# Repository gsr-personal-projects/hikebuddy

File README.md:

# hikebuddy
An ESP32 based hike/bike computer with weather monitoring, GPS tracking and BLE sensor support (and a general purpose development board)

This project has moved to its own home at https://github.com/hikebuddy32.

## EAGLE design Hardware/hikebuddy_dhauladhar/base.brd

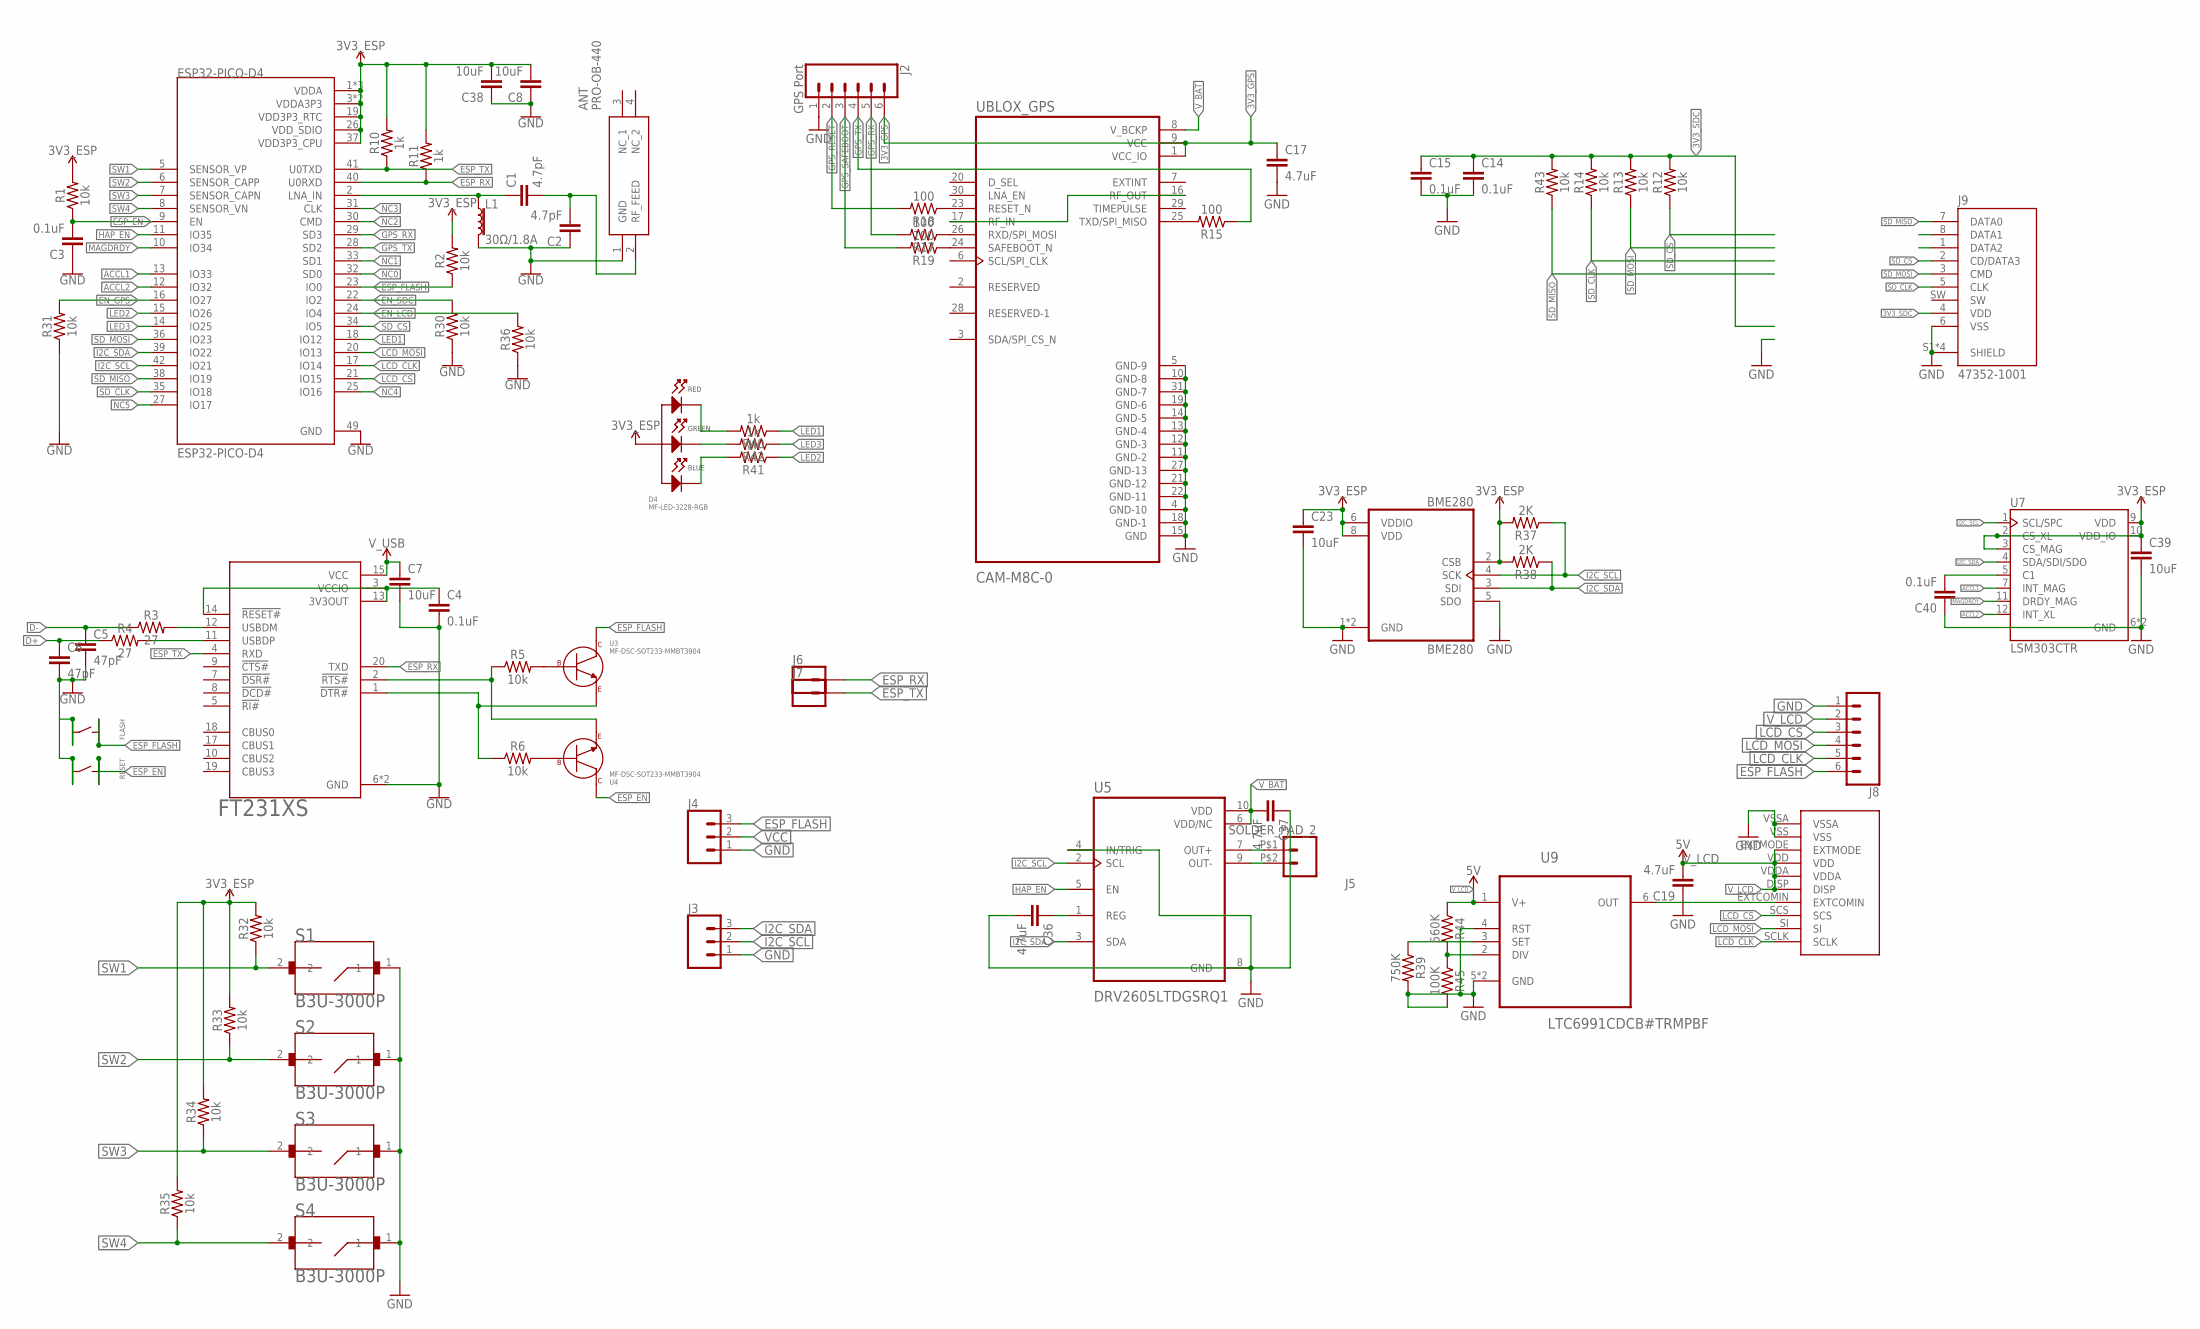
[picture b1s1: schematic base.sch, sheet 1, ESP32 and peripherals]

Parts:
ANT: PRO-OB-440; PRO-OB-440_1
BME280: BME280; PSON65P250X250X100-8N
C1, C2: 4.7pF; C0603
C3, C4, C14, C15, C40: 0.1uF; C0603
C5, C6: 47pF; C0603
C7, C8, C23, C38, C39: 10uF; C0603
C17, C19, C36, C37: 4.7uF; C0603
D4: MF-LED-3228-RGB; PLCC4
ESP32-PICO-D4: ESP32-PICO-D4; PQFN50P700X700X104-49N
FLASH: MF-SW-TACT-4.2MM; TACT4.2MM
FT231: FT231XS; TSSOP20
J2: GPS Port; 1X06_LOCK
J3, J4: CONN_03LOCK; 1X03_LOCK
J5: SOLDER_PAD_2
J6, J7: CONN_01; 1X01
J8: CONN_06LOCK; 1X06_LOCK
J9: 47352-1001; MOLEX_47352-1001
L1: 30Ω/1.8A; L0603; MPN 744761016C
R1, R2, R5, R6, R12, R13, R14, R30, R31, R32, R33, R34, R35, R36, R43: 10k; R0603
R3, R4: 27; R0603
R10, R11, R40, R41, R42: 1k; R0603
R15, R17, R18, R19: 100; R0603
R37, R38: 2K; R0603
R39: 750K; R0603
R44: 560K; R0603
R45: 100K; R0603
RESET: MF-SW-TACT-4.2MM; TACT4.2MM
S1, S2, S3, S4: B3U-3000P; SW_B3U-3000P
U3, U4: MF-DSC-SOT233-MMBT3904; SOT-23-3
U5: DRV2605LTDGSRQ1; SOP50P490X110-10N
U7: LSM303CTR; LGA-12
U9: LTC6991CDCB#TRMPBF; DFN
U$5: 51441-1093; FH12-10S-0.5SH; MPN 51441-1093
UBLOX_GPS: CAM-M8C-0; LCC100P960X1400X210-31N

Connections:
3V3_GPS: C17.1, J2.6, UBLOX_GPS.1 (VCC_IO), UBLOX_GPS.9 (VCC); also elsewhere on the board
3V3_SDC: C14.1, C15.1, J9.4 (VDD), R12.2, R13.2, R14.2, R43.2; also elsewhere on the board
ACCL1: ESP32-PICO-D4.13 (IO33), U7.7 (INT_MAG)
ACCL2: ESP32-PICO-D4.12 (IO32), U7.12 (INT_XL)
D+: C6.1, R4.1; also elsewhere on the board
D-: C5.1, R3.1; also elsewhere on the board
EN_GPS: ESP32-PICO-D4.16 (IO27), R31.2; also elsewhere on the board
EN_LCD: ESP32-PICO-D4.24 (IO4), R36.2; also elsewhere on the board
EN_SDC: ESP32-PICO-D4.22 (IO2), R30.2; also elsewhere on the board
ESP_EN: C3.2, ESP32-PICO-D4.9 (EN), R1.1, RESET.P$1, RESET.P$2, U4.P$3 (COLLECTOR)
ESP_FLASH: ESP32-PICO-D4.23 (IO0), FLASH.P$1, FLASH.P$2, J4.3, J8.6, R2.1, U3.P$3 (COLLECTOR)
ESP_RX: ESP32-PICO-D4.40 (U0RXD), FT231.20 (TXD), J6.1, R11.1
ESP_TX: ESP32-PICO-D4.41 (U0TXD), FT231.4 (RXD), J7.1, R10.1
GND: ANT.1 (GND), BME280.1 (GND), BME280.5 (SDO), BME280.7 (GND), C2.1, C3.1, C4.2, C5.2, C6.2, C7.2, C8.1, C14.2, C15.2, C17.2, C19.1, C23.2, C36.2, C37.1, C38.1, C39.2, C40.1, ESP32-PICO-D4.49 (GND), FLASH.P$3, FLASH.P$4, FT231.6 (GND), FT231.16 (GND), J2.1, J3.1, J4.1, J8.1, J9.6 (VSS), J9.S1 (SHIELD), J9.S2 (SHIELD), J9.S3 (SHIELD), J9.S4 (SHIELD), L1.2, R30.1, R31.1, R36.1, R39.2, R45.2, RESET.P$3, RESET.P$4, S1.1, S2.1, S3.1, S4.1, U5.4 (IN/TRIG), U5.8 (GND), U7.6 (GND), U7.8 (GND), U9.4 (RST), U9.5 (GND), U9.7 (GND), U$5.VSS, U$5.VSSA, UBLOX_GPS.4 (GND-10), UBLOX_GPS.5 (GND-9), UBLOX_GPS.10 (GND-8), UBLOX_GPS.11 (GND-2), UBLOX_GPS.12 (GND-3), UBLOX_GPS.13 (GND-4), UBLOX_GPS.14 (GND-5), UBLOX_GPS.15 (GND), UBLOX_GPS.18 (GND-1), UBLOX_GPS.19 (GND-6), UBLOX_GPS.21 (GND-12), UBLOX_GPS.22 (GND-11), UBLOX_GPS.27 (GND-13), UBLOX_GPS.31 (GND-7); also elsewhere on the board
GPS_RESET: J2.2, R18.2
GPS_RX: ESP32-PICO-D4.29 (SD3), J2.5, R17.2
GPS_SAFEBOOT: J2.3, R19.2
GPS_TX: ESP32-PICO-D4.28 (SD2), J2.4, R15.1
HAP_EN: ESP32-PICO-D4.11 (IO35), U5.5 (EN)
I2C_SCL: BME280.4 (SCK), ESP32-PICO-D4.42 (IO21), J3.2, R37.1, U5.2 (SCL), U7.1 (SCL/SPC); also elsewhere on the board
I2C_SDA: BME280.3 (SDI), ESP32-PICO-D4.39 (IO22), J3.3, R38.1, U5.3 (SDA), U7.4 (SDA/SDI/SDO); also elsewhere on the board
LCD_CLK: ESP32-PICO-D4.17 (IO14), J8.5, U$5.SCLK
LCD_CS: ESP32-PICO-D4.21 (IO15), J8.3, U$5.SCS
LCD_MOSI: ESP32-PICO-D4.20 (IO13), J8.4, U$5.SI
LED1: ESP32-PICO-D4.18 (IO12), R40.1
LED2: ESP32-PICO-D4.15 (IO26), R41.1
LED3: ESP32-PICO-D4.14 (IO25), R42.1
MAGDRDY: ESP32-PICO-D4.10 (IO34), U7.11 (DRDY_MAG)
unnamed: C1.1, ESP32-PICO-D4.2 (LNA_IN), L1.1
unnamed: ANT.2 (RF_FEED), C1.2, C2.2
unnamed: R5.2, U3.P$1 (BASE)
unnamed: R6.2, U4.P$1 (BASE)
unnamed: C4.1, FT231.3 (VCCIO), FT231.13 (3V3OUT), FT231.14 (!RESET#)
unnamed: FT231.12 (USBDM), R3.2
unnamed: FT231.11 (USBDP), R4.2
unnamed: FT231.2 (!RTS#), R5.1, U4.P$2 (EMITTER)
unnamed: FT231.1 (!DTR#), R6.1, U3.P$2 (EMITTER)
unnamed: C40.2, U7.5 (C1)
unnamed: D4.P$2 (CATHODE_RED), R40.2
unnamed: R15.2, UBLOX_GPS.25 (TXD/SPI_MISO)
unnamed: R17.1, UBLOX_GPS.26 (RXD/SPI_MOSI)
unnamed: D4.P$3 (CATHODE_GREEN), R42.2
unnamed: D4.P$4 (CATHODE_BLUE), R41.2
unnamed: UBLOX_GPS.16 (RF_OUT), UBLOX_GPS.17 (RF_IN)
unnamed: U9.6 (OUT), U$5.EXTCOMIN
unnamed: R18.1, UBLOX_GPS.23 (RESET_N)
unnamed: R19.1, UBLOX_GPS.24 (SAFEBOOT_N)
unnamed: R39.1, U9.3 (SET)
unnamed: C36.1, U5.1 (REG)
unnamed: R44.2, R45.1, U9.2 (DIV)
unnamed: J5.P$2 (2), U5.9 (OUT-)
unnamed: J5.P$1 (1), U5.7 (OUT+)
NC0: ESP32-PICO-D4.32 (SD0)
NC1: ESP32-PICO-D4.33 (SD1)
NC2: ESP32-PICO-D4.30 (CMD)
NC3: ESP32-PICO-D4.31 (CLK)
NC4: ESP32-PICO-D4.25 (IO16)
NC5: ESP32-PICO-D4.27 (IO17)
SD_CLK: ESP32-PICO-D4.35 (IO18), J9.5 (CLK), R14.1
SD_CS: ESP32-PICO-D4.34 (IO5), J9.2 (CD/DATA3), R12.1
SD_MISO: ESP32-PICO-D4.38 (IO19), J9.7 (DATA0), R43.1
SD_MOSI: ESP32-PICO-D4.36 (IO23), J9.3 (CMD), R13.1
SW1: ESP32-PICO-D4.5 (SENSOR_VP), R32.1, S1.2
SW2: ESP32-PICO-D4.6 (SENSOR_CAPP), R33.1, S2.2
SW3: ESP32-PICO-D4.7 (SENSOR_CAPN), R34.1, S3.2
SW4: ESP32-PICO-D4.8 (SENSOR_VN), R35.1, S4.2
VCC: BME280.2 (CSB), BME280.6 (VDDIO), BME280.8 (VDD), C8.2, C23.1, C38.2, C39.1, D4.P$1 (ANODE), ESP32-PICO-D4.1 (VDDA), ESP32-PICO-D4.3 (VDDA3P3), ESP32-PICO-D4.4 (VDDA3P3), ESP32-PICO-D4.19 (VDD3P3_RTC), ESP32-PICO-D4.26 (VDD_SDIO), ESP32-PICO-D4.37 (VDD3P3_CPU), ESP32-PICO-D4.43 (VDDA), ESP32-PICO-D4.46 (VDDA), J4.2, R1.2, R2.2, R10.2, R11.2, R32.2, R33.2, R34.2, R35.2, R37.2, R38.2, U7.2 (CS_XL), U7.3 (CS_MAG), U7.9 (VDD), U7.10 (VDD_IO); also elsewhere on the board
V_BAT: C37.2, U5.6 (VDD/NC), U5.10 (VDD), UBLOX_GPS.8 (V_BCKP); also elsewhere on the board
V_LCD: C19.2, J8.2, R44.1, U9.1 (V+), U$5.DISP, U$5.EXTMODE, U$5.VDD, U$5.VDDA; also elsewhere on the board
V_USB: C7.1, FT231.15 (VCC); also elsewhere on the board

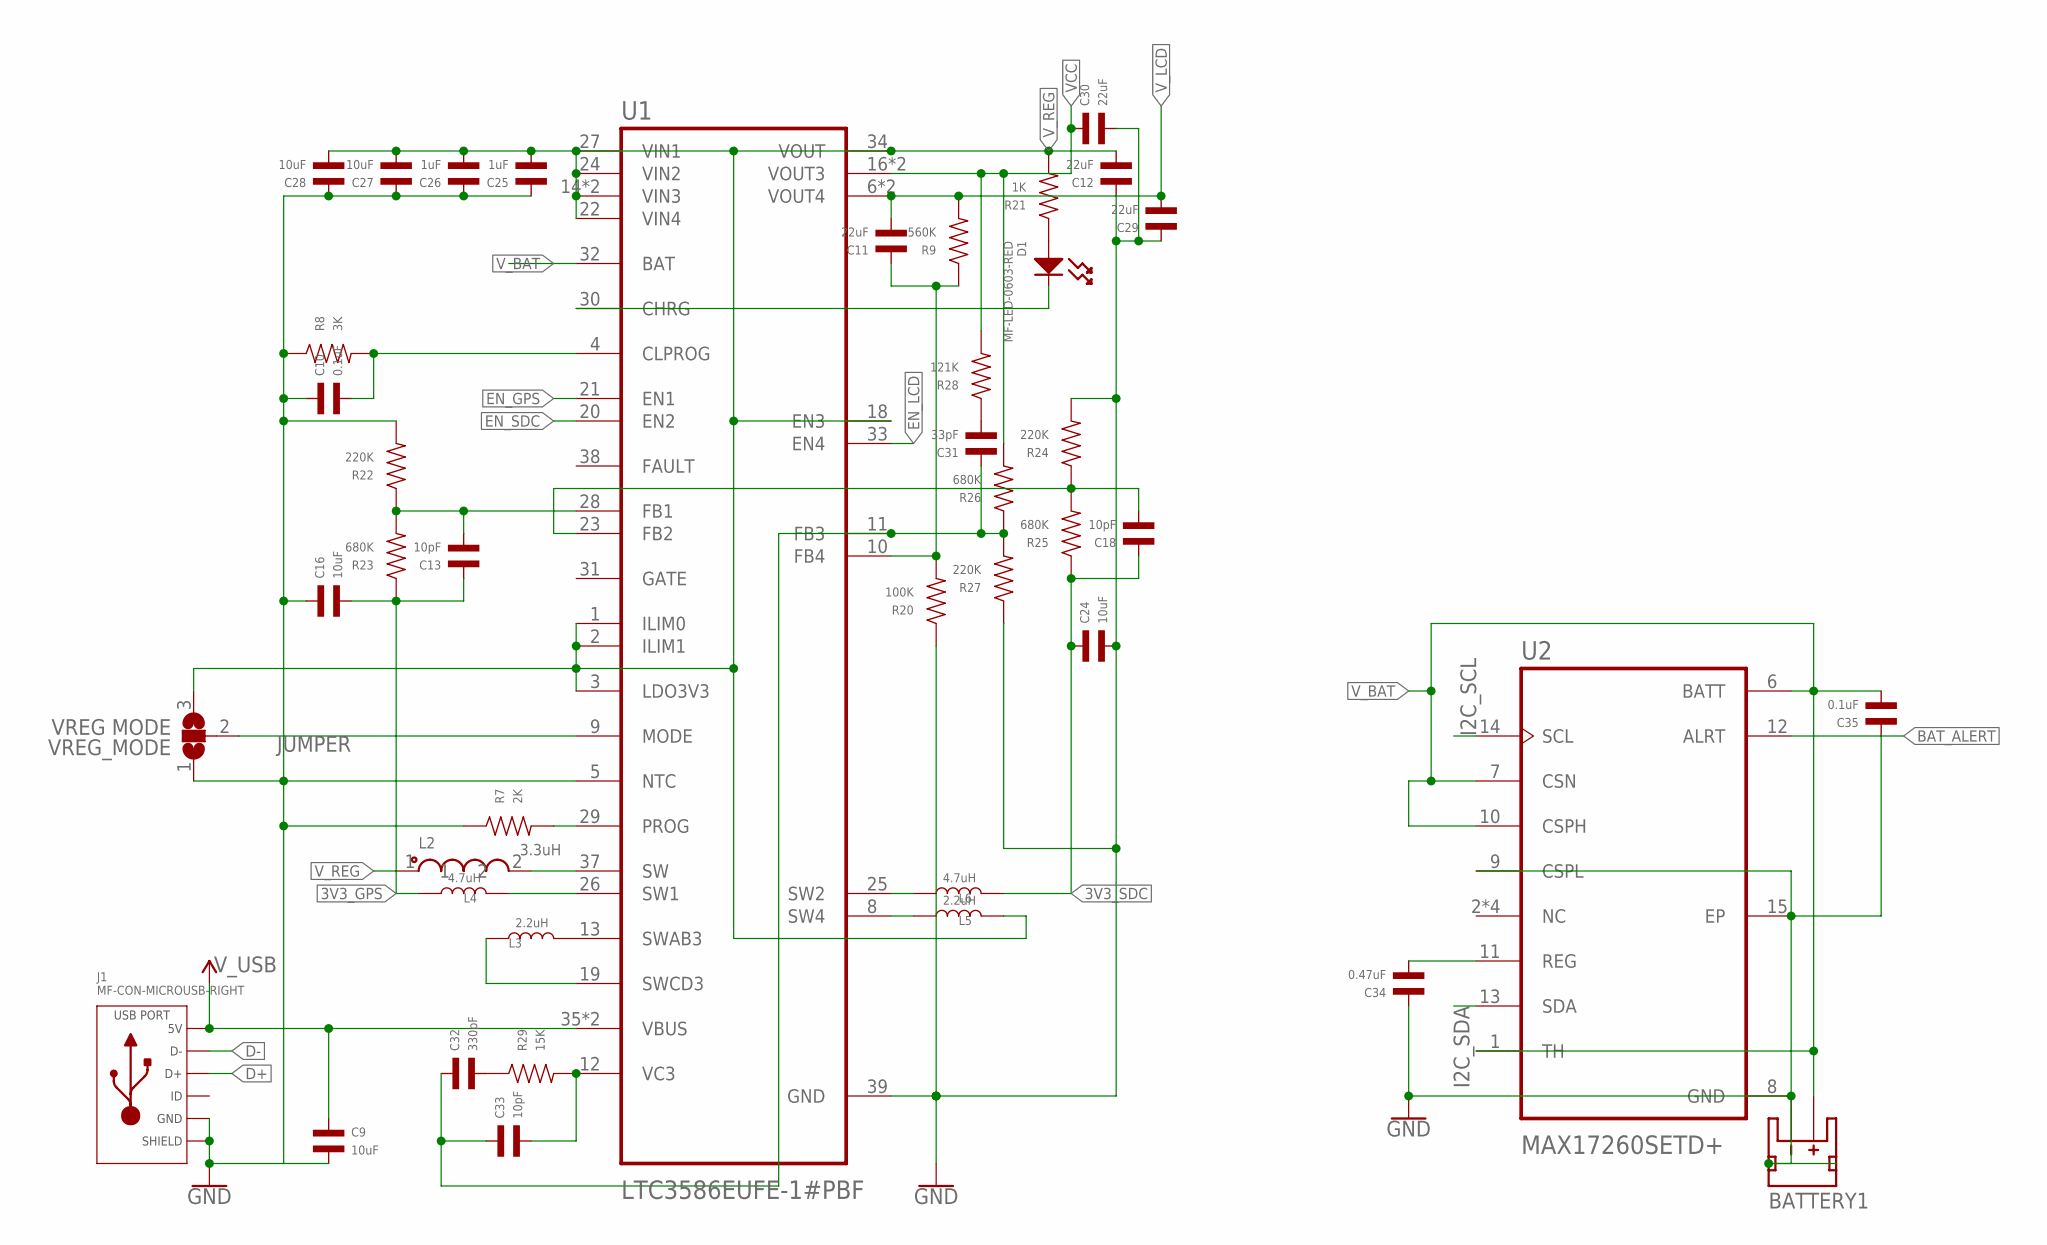
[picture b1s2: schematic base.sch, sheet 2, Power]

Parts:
BATTERY1: JST_2MM_MALE; JST-2-SMD
C9: 10uF; C1206
C10, C35: 0.1uF; C0603
C11, C12, C29, C30: 22uF; C0603
C13, C18, C33: 10pF; C0603
C16, C24, C27, C28: 10uF; C0603
C25, C26: 1uF; C0603
C31: 33pF; C0603
C32: 330pF; C0603
C34: 0.47uF; C0603
D1: MF-LED-0603-RED; LED0603
J1: MF-CON-MICROUSB-RIGHT; MICROUSB-RIGHT
L2: 3.3uH; INDP_LPS4018-472MRB; MPN LPS4018-472MRB
L3, L5: 2.2uH; L1210; MPN L1210R2R2MDWIT
L4, L6: 4.7uH; L1210; MPN L1210R4R7MDWIT
R7: 2K; R0603
R8: 3K; R0603
R9: 560K; R0603
R20: 100K; R0603
R21: 1K; R0603
R22, R24, R27: 220K; R0603
R23, R25, R26: 680K; R0603
R28: 121K; R0603
R29: 15K; R0603
U1: LTC3586EUFE-1#PBF; QFN40P600X400X80-39N
U2: MAX17260SETD+; SON40P300X300X80-15N
VREG_MODE: VREG MODE; SJ_2

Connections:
3V3_GPS: C13.P$1, C16.P$2, L4.P$1, R23.P$1; also elsewhere on the board
3V3_SDC: C18.P$1, C24.P$1, L6.P$2, R25.P$1; also elsewhere on the board
BAT_ALERT: U2.12 (ALRT)
D+: J1.3 (D+); also elsewhere on the board
D-: J1.2 (D-); also elsewhere on the board
EN_GPS: U1.21 (EN1); also elsewhere on the board
EN_LCD: U1.33 (EN4); also elsewhere on the board
EN_SDC: U1.20 (EN2); also elsewhere on the board
GND: BATTERY1.1 (-), BATTERY1.NC1 (PAD1), BATTERY1.NC2 (PAD2), C9.P$2, C10.P$1, C12.P$1, C16.P$1, C24.P$2, C25.P$1, C26.P$1, C27.P$1, C28.P$1, C29.P$1, C30.P$2, C34.P$1, C35.P$1, J1.5 (GND), J1.S1 (SLD), J1.S2 (SLD), J1.S3 (SLD), J1.S4 (SLD), J1.S5 (SLD), J1.S6 (SLD), R7.P$1, R8.P$1, R20.P$1, R22.P$2, R24.P$2, R27.P$1, U1.5 (NTC), U1.39 (GND), U2.8 (GND), U2.9 (CSPL), U2.15 (EP), VREG_MODE.1; also elsewhere on the board
I2C_SCL: U2.14 (SCL); also elsewhere on the board
I2C_SDA: U2.13 (SDA); also elsewhere on the board
JUMPER: U1.9 (MODE), VREG_MODE.2
unnamed: R7.P$2, U1.29 (PROG)
unnamed: C10.P$2, R8.P$2, U1.4 (CLPROG)
unnamed: C11.P$1, R9.P$1, R20.P$2, U1.10 (FB4)
unnamed: L3.P$2, U1.13 (SWAB3)
unnamed: C31.P$1, C32.P$1, C33.P$1, R26.P$1, R27.P$2, U1.11 (FB3)
unnamed: L2.2, U1.37 (SW)
unnamed: D1.CATHODE, U1.30 (CHRG)
unnamed: D1.ANODE, R21.P$1
unnamed: L3.P$1, U1.19 (SWCD3)
unnamed: L4.P$2, U1.26 (SW1)
unnamed: C13.P$2, R22.P$1, R23.P$2, U1.28 (FB1)
unnamed: L5.P$1, U1.8 (SW4)
unnamed: C18.P$2, R24.P$1, R25.P$2, U1.23 (FB2)
unnamed: L6.P$1, U1.25 (SW2)
unnamed: C31.P$2, R28.P$1
unnamed: C33.P$2, R29.P$2, U1.12 (VC3)
unnamed: C32.P$2, R29.P$1
unnamed: C34.P$2, U2.11 (REG)
VCC: C30.P$1, R26.P$2, R28.P$2, U1.16 (VOUT3), U1.17 (VOUT3); also elsewhere on the board
V_BAT: BATTERY1.2 (+), C35.P$2, U1.32 (BAT), U2.1 (TH), U2.6 (BATT), U2.7 (CSN), U2.10 (CSPH); also elsewhere on the board
V_LCD: C11.P$2, C29.P$2, R9.P$2, U1.6 (VOUT4), U1.7 (VOUT4); also elsewhere on the board
V_REG: C12.P$2, C25.P$2, C26.P$2, C27.P$2, C28.P$2, L2.1, L5.P$2, R21.P$2, U1.1 (ILIM0), U1.2 (ILIM1), U1.3 (LDO3V3), U1.14 (VIN3), U1.15 (VIN3), U1.18 (EN3), U1.22 (VIN4), U1.24 (VIN2), U1.27 (VIN1), U1.34 (VOUT), VREG_MODE.3
V_USB: C9.P$1, J1.1 (5V), U1.35 (VBUS), U1.36 (VBUS); also elsewhere on the board

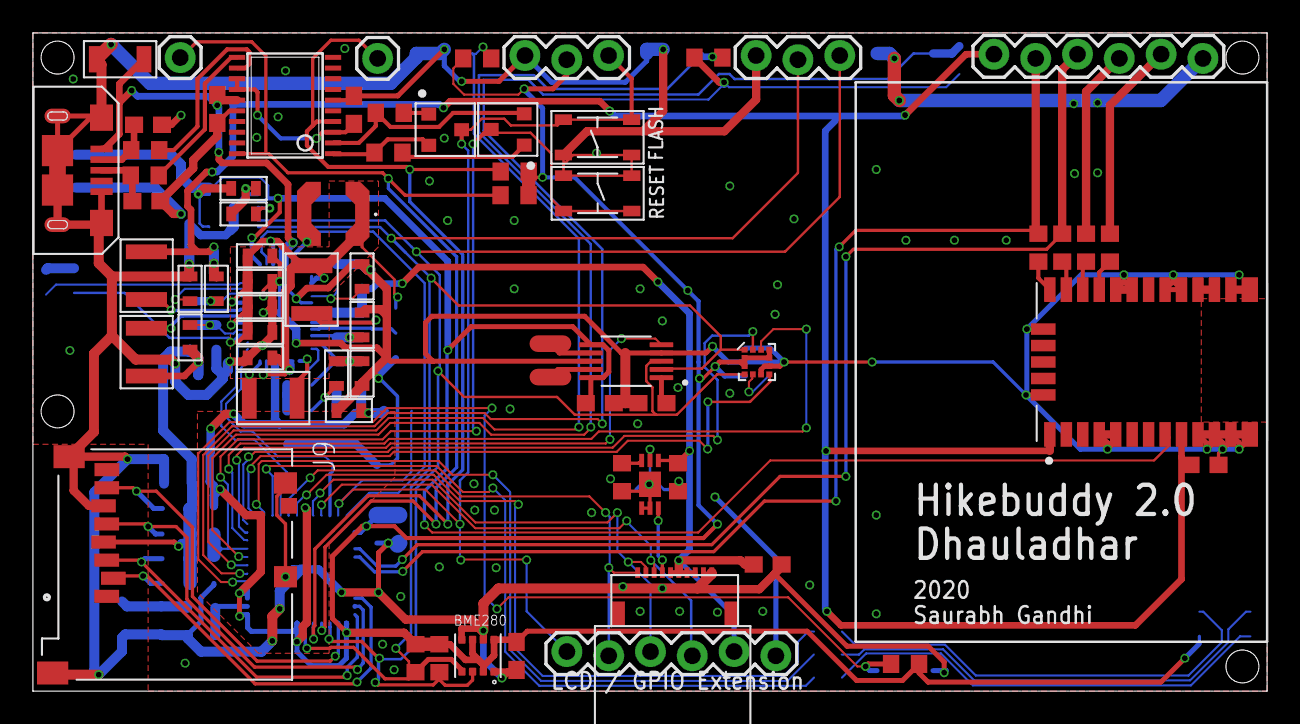
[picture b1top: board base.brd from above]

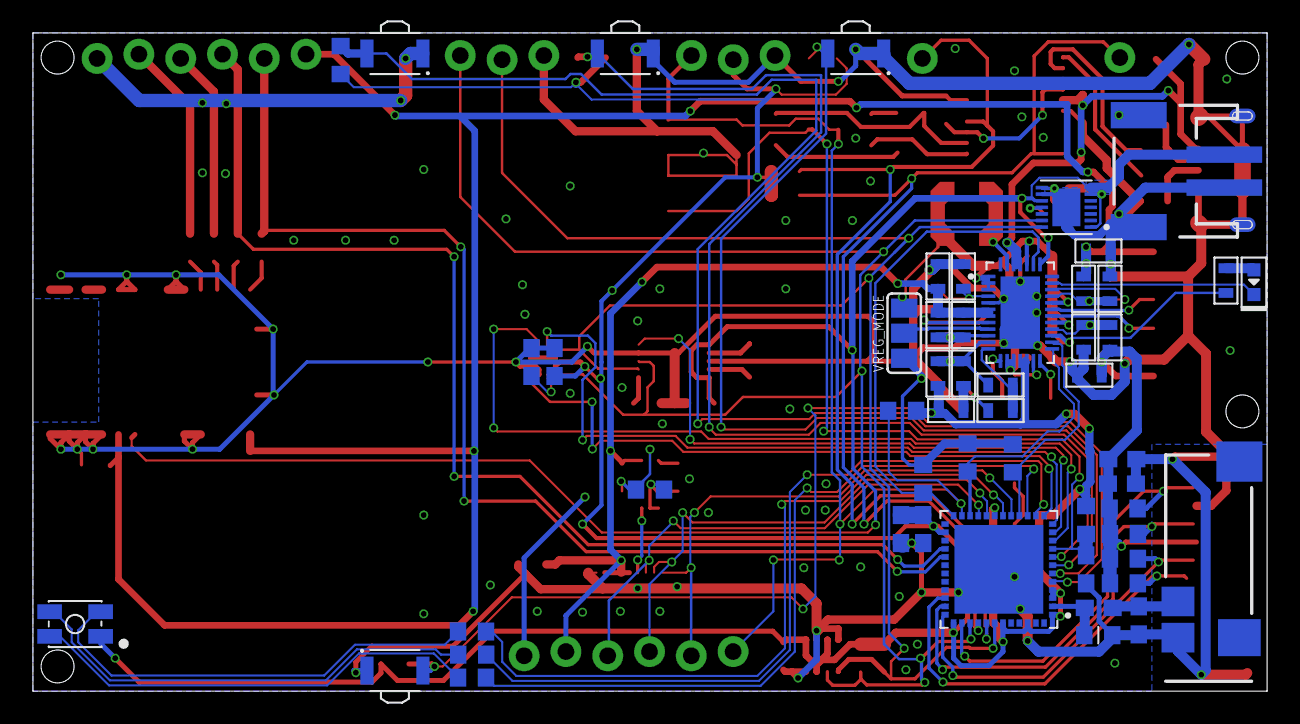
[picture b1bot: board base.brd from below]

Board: 2 copper layers, 75.0 x 40.0 mm, 119 parts (52 on the bottom side), 84 nets.

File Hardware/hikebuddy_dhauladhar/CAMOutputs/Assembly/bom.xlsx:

Designator | Value | Device | Package | MOUSER_PART_NUMBER | MPN | DIGIKEY_PART_NUMBER | 4UCONN | Quantity
ANT | PRO-OB-440 | PRO-OB-440 | PRO-OB-440_1 |  | PRO-OB-440 | 1532-1001-1-ND |  | 1
BATTERY1 |  | JST_2MM_MALE | JST-2-SMD |  | S2B-PH-SM4-TB(LF)(SN) | 455-1749-1-ND |  | 1
BME280 | BME280 | BME280 | PSON65P250X250X100-8N | 262-BME280 | BME280 | 828-1063-1-ND |  | 1
C1, C2 | 4.7pF | 4.7PF-0603-50V-5% | C0603 | 603-CC603CRNPO9BN4R7 | CC0603CRNPO9BN4R7 | 311-1740-1-ND |  | 2
C3, C4, C10, C14, C15, C35, C40 | 0.1uF | 0.1UF-0603-25V-(+80/-20%) | C0603 | 603-C0603ZRY5V8BB104 | CC0603ZRY5V8BB104 | 311-1087-1-ND |  | 7
C5, C6 | 47pF | 47PF-0603-50V-5% | C0603 | 603-CC603JRNPO9BN470 | CC0603JRNPO9BN470 | 311-1065-1-ND |  | 2
C7, C8, C16, C23, C24, C27, C28, C38, C39 | 10uF | 2.2UF-0603-10V-20% | C0603 | 603-CC603KRX5R5BB106 | CC0603KRX5R5BB106 | 311-1781-1-ND |  | 9
C9 | 10uF | CAPACITOR_NP_1206 | C1206 | 603-CC126ZRY5V6BB106 | CC1206ZRY5V6BB106 | 311-2007-1-ND |  | 1
C11, C12, C29, C30 | 22uF | CAPACITOR_NP_0603 | C0603 | 603-CC603MRX5R5BB226 | CC0603MRX5R5BB226 | 311-1815-1-ND |  | 4
C13, C18, C33 | 10pF | CAPACITOR_NP_0603 | C0603 | 603-C0603JRNPO9BN100 | CC0603JRNPO9BN100 | 311-1058-1-ND |  | 3
C17, C19, C36, C37 | 4.7uF | 0.1UF-0603-25V-5% | C0603 | 603-CC603KRX5R6BB475 | CC0603KRX5R6BB475 | 311-1455-1-ND |  | 4
C25, C26 | 1uF | CAPACITOR_NP_0603 | C0603 | 603-CC603KRX5R8BB105 | CC0603KRX5R8BB105 | 311-1445-1-ND |  | 2
C31 | 33pF | CAPACITOR_NP_0603 | C0603 | 603-C0603JRNPO9BN330 | CC0603JRNPO9BN330 | 311-1064-1-ND |  | 1
C32 | 330pF | CAPACITOR_NP_0603 | C0603 | 603-C0603KRX7R9BB331 | CC0603KRX7R9BB331 | 311-1186-1-ND |  | 1
C34 | 0.47uF | CAPACITOR_NP_0603 | C0603 | 603-CC603ZRY5V6BB474 | CC0603ZRY5V6BB474 | 311-4114-1-ND |  | 1
D1 | MF-LED-0603-RED | LED_SINGLE-0603-RED | LED0603 | 859-LTST-C190KRKT | LTST-C190KRKT | 160-1436-1-ND |  | 1
D4 | MF-LED-3228-RGB | LED_RGB_CA_PLCC4 | PLCC4 | 630-ASMB-MTB0-0A3A2 | ASMB-MTB0-0A3A2 | 516-3279-1-ND |  | 1
ESP32-PICO-D4 | ESP32-PICO-D4 | ESP32-PICO-D4 | PQFN50P700X700X104-49N | 356-ESP32-PICO-D4 | ESP32-PICO-D4 | 1904-1029-1-ND |  | 1
FLASH, RESET | MF-SW-TACT-4.2MM | TACT_4.2MM | TACT4.2MM | 611-PTS810SJG250SMTR | PTS810 SJG 250 SMTR LFS | CKN10504CT-ND |  | 2
FT231 | FT231XS | FT231XS-UTSSOP20 | TSSOP20 | 895-FT231XS-U | FT231XS-U | 768-1156-5-ND |  | 1
J1 | MF-CON-MICROUSB-RIGHT | USB_MICRO_RIGHT | MICROUSB-RIGHT | 649-10118193-0001LF | 10118193-0001LF | 609-4616-1-ND |  | 1
L1 | 30ohm/1.8A | INDUCTOR | L0603 | 710-744761016C | 744761016C | 732-1746-1-ND |  | 1
L2 | 3.3uH | LPS4018-472MRB | INDP_LPS4018-472MRB | 994-LPS4018-472MRB | LPS4018-472MRB |  |  | 1
L3, L5 | 2.2uH | INDUCTOR_1210 | L1210 | 80-L1210R2R2MDWIT | L1210R2R2MDWIT | 399-9598-1-ND |  | 2
L4, L6 | 4.7uH | INDUCTOR_1210 | L1210 | 80-L1210R4R7MDWIT | L1210R4R7MDWIT | 399-9599-1-ND |  | 2
R1, R2, R5, R6, R12, R13, R14, R30, R31, R32, R33, R34, R35, R36, R43 | 10k | 10KOHM-0603-1/10W-1% | R0603 | 603-RC0603FR-0710KL | RC0603FR-0710KL | 311-10.0KHRCT-ND |  | 15
R3, R4 | 27 | 27OHM-0603-1/10W-1% | R0603 | 603-RC0603FR-0727RL | RC0603FR-0727RL | 311-27.0HRCT-ND |  | 2
R7, R37, R38 | 2K | RESISTOR_0603 | R0603 | 603-RC0603FR-072KL | RC0603FR-072KL | 311-2.00KHRCT-ND |  | 3
R8 | 3K | RESISTOR_0603 | R0603 | 603-RT0603BRD073KL | RT0603BRD073KL | YAG1657CT-ND |  | 1
R9, R44 | 560K | RESISTOR_0603 | R0603 | 603-RC0603FR-07560KL | RC0603FR-07560KL | 311-560KHRCT-ND |  | 2
R10, R11, R21, R40, R41, R42 | 1k | 1KOHM-0603-1/10W-1% | R0603 | 603-RC0603FR-071KL | RC0603FR-071KL | 311-1.00KHRCT-ND |  | 6
R15, R17, R18, R19 | 100 | 1KOHM-0603-1/10W-1% | R0603 | 603-RC0603FR-07100RL | RC0603FR-07100RL | 311-100HRCT-ND |  | 4
R20, R45 | 100K | RESISTOR_0603 | R0603 | 603-RT0603BRD07100KL | RT0603BRD07100KL | YAG1235CT-ND |  | 2
R22, R24, R27 | 220K | RESISTOR_0603 | R0603 | 603-AC0603FR-07220KL | AC0603FR-07220KL | YAG3579CT-ND |  | 3
R23, R25, R26 | 680K | RESISTOR_0603 | R0603 | 603-RC0603FR-07680KL | RC0603FR-07680KL | 311-680KHRCT-ND |  | 3
R28 | 121K | RESISTOR_0603 | R0603 | 603-RC0603FR-07121KL | RC0603FR-07121KL | 311-121KHRCT-ND |  | 1
R29 | 15K | RESISTOR_0603 | R0603 | 603-RC0603FR-0715KL | RC0603FR-0715KL | 311-15.0KHRCT-ND |  | 1
R39 | 750K | 1KOHM-0603-1/10W-1% | R0603 | 603-RC0603FR-07750KL | RC0603FR-07750KL | 311-750KHRCT-ND |  | 1
S1, S2, S3, S4 | B3U-3000P | B3U-3000P | SW_B3U-3000P | 653-B3U-3000P | B3U-3000P | SW1022CT-ND |  | 4
U$5 | 51441-1093 | LS027B_LCD_SHARPFH12-10S-0.5SH | FH12-10S-0.5SH | 514411093 | 514411093 | WM6474CT-ND |  | 1
U1 | LTC3586EUFE-1#PBF | LTC3586EUFE-3#TRPBF | QFN -38 Analog Devices | 584-LTC3586EUFE#PBF | LTC3586EUFE#PBF | LTC3586EUFE#PBF-ND |  | 1
U2 | MAX17260SETD+ | MAX17260SETD+ | TDFN-14 Maxim | 700-MAX17260SETD+ | MAX17260SETD+ | MAX17260SETD+T-ND |  | 1
U3, U4 | MF-DSC-SOT233-MMBT3904 | NPN_BJTMMBT3904_SOT-23-3 | SOT-23-3 | 863-MMBT3904LT1G | MMBT3904LT1G | MMBT3904LT1GOSTR-ND |  | 2
U5 | DRV2605LTDGSRQ1 | DRV2605LTDGSRQ1 | TFSOP-10 Texas Instruments | 595-DRV2605LTDGSRQ1 | DRV2605LTDGSRQ1 | 296-43247-2-ND |  | 1
U7 | LSM303CTR | LSM303CTR | LGA-12 STMicroelectronics | 511-LSM303AGRTR | LSM303AGRTR | 497-16527-1-ND |  | 1
U9 | LTC6991CDCB#TRMPBF | LTC6991CS6TRMPBFDFN | DFN | 584-LTC6991CDCBTRPBF | LTC6991CDCB#TRMPBF | LTC6991CDCB#TRMPBFCT-ND |  | 1
UBLOX_GPS | CAM-M8C-0 | CAM-M8C-0 | SMD-31 u-blox |  | CAM-M8C-0-10 | 672-CAM-M8C-0-10CT-ND |  | 1
SD-CARD | MF-MICROSD | SD_CARD_SLOT_MICRO_RIGHT | MF-MICROSD |  | 15882 |  | 15882 | 1

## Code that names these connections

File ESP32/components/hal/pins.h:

/** @file board_pins.h */
#ifndef PINS_H
#define PINS_H

#include "sdkconfig.h"

//#ifdef CONFIG_HB_BOARD_V0

#define PCA_0_LED_BLE       0
#define PCA_0_LED_GRN       1
#define PCA_0_LED_RED       2
#define PCA_0_PWR_GPS       3
#define PCA_0_PWR_SDC       4
#define PCA_0_PWR_LCD       6
#define PCA_0_RST_GPS       7
#define PCA_0_EN_LCD        5

#define PCA_1_BTN_LEFT      8
#define PCA_1_BTN_RIGHT     9
#define PCA_1_BTN_UP       10
#define PCA_1_BTN_DOWN     11
#define PCA_1_BTN_SEL      12
#define PCA_1_INT_ACL1     13
#define PCA_1_INT_ACL2     14
#define PCA_1_INT_MAG      15

#define PIN_LCD_CLK        14
#define PIN_LCD_MOSI       13
#define PIN_LCD_CS         15

#define PIN_SDC_CLK        18
#define PIN_SDC_MISO       19
#define PIN_SDC_MOSI       23
#define PIN_SDC_CS          5

#define PIN_GPIO_INT        4
#define PIN_USB_DETECT     27
#define PIN_CHG_STAT       34

#define PIN_I2C_CLK        21
#define PIN_I2C_DATA       22

#define PIN_UART2_RX       32
#define PIN_UART2_TX       33

#define PIN_DAC_VIB         2
#define PIN_DAC_BUZ         1

#define ADC1_VBAT_SENSE     7

#endif // PINS_H

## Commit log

2019-03-19 Hardware v1 files
2019-03-19 fixed gitignore
2019-03-19 added hardware reference files
2019-03-19 added esp-idf as a submodule
2019-03-19 initial firmware development setup
2019-03-19 added basic modules
2019-03-19 more modules
2019-03-22 added 3D models for most PCB parts
2019-03-25 added lvgl submodule
2019-04-12 removed bme and lvgl submodules
2019-04-12 Reorganized components
2019-05-14 mlcd working
2019-05-15 lvgl, input working
2019-05-21 lvgl and bme working example
2019-05-22 bme_demo_gui fixed all
2019-10-18 last commit before starting V2
2020-01-09 digikey_cs_v0
2020-01-21 remove backups

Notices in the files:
parts and their libraries:
SparkFun-Capacitors: Licensing: Creative Commons ShareAlike 4.0 International - https://creativecommons.org/licenses/by-sa/4.0
